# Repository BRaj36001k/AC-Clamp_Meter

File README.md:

**⚡ AC Clamp Meter**

A KiCad-based PCB design for a non-invasive AC measurement device using a Current Transformer (CT) sensor. Built as part of an EEE hardware project.
_____________________________________________________________
**📌 Overview**

This project implements an **AC Clamp Meter** circuit that measures alternating current without breaking the circuit. The design uses a split-core CT sensor, a signal conditioning front-end, and outputs a calibrated voltage proportional to the measured current.
---------------------------------------------------------------------------------------
|                Parameter              |                     Value                   |
|---------------------------------------|---------------------------------------------|
| Measurement Range                     |     0 – 110A AC (adjustable)                |
| CT Sensor                             |    SCT-013 / YHDC (30A or 100A variant)     |
| Output                                |          0–3.3V analog (ADC-ready)          |
| PCB Tool                              |                  KiCad 7.x                  |
---------------------------------------------------------------------------------------
______________________________________________________________
**🔌 How It Works**

CT Sensor (clamp)
      │
      ▼
3.5mm Jack Input
      │
      ▼
Signal Conditioning
(R1, R2, R3, R4 + D12 + C1)
      │
      ▼
Arduino Nano ADC Pin
      │
      ▼
Firmware Processing
      │
      ▼
I2C OLED Display
(GND / VCC / SDA / SCL)

__________________________________________________________________

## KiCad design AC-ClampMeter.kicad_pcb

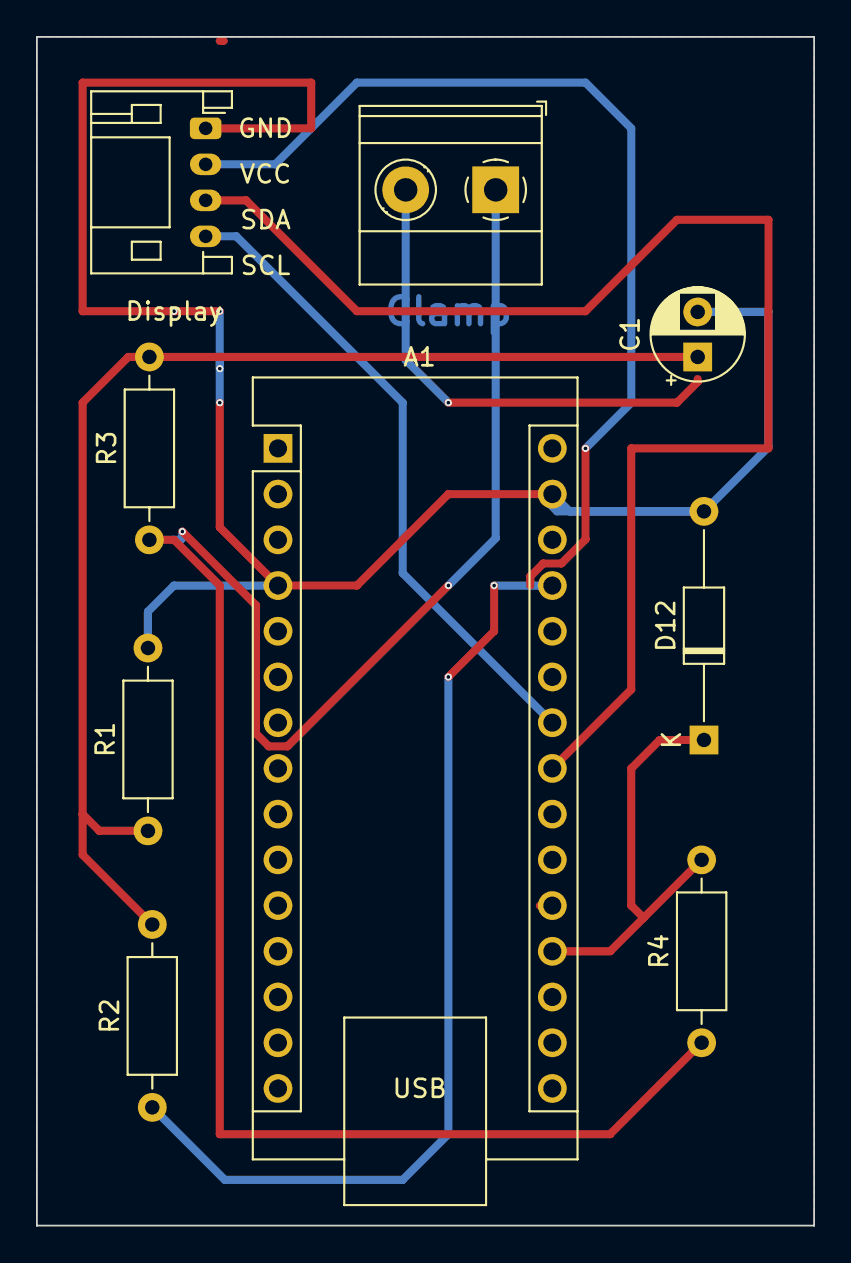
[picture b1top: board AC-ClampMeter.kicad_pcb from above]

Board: 2 copper layers, 43.2 x 66.0 mm, 8 parts (0 on the bottom side), 7 nets.

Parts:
A1: locked; Arduino_Nano
C1: 10uf 16V; CP_Radial_D5.0mm_P2.50mm
D12: 5V; D_DO-35_SOD27_P12.70mm_Horizontal
Display: 16x2 LCD with I2C; JST_PH_S4B-PH-K_1x04_P2.00mm_Horizontal
R1, R2: 10k; R_Axial_DIN0207_L6.3mm_D2.5mm_P10.16mm_Horizontal
R3: 68E; R_Axial_DIN0207_L6.3mm_D2.5mm_P10.16mm_Horizontal
R4: 1k; R_Axial_DIN0207_L6.3mm_D2.5mm_P10.16mm_Horizontal

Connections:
+5V: A1.27 (+5V), R2.1
A0: A1.19 (A0), D12.1 (K), R4.2
A4: A1.23 (A4), Display.3
A5: A1.24 (A5), Display.4
GND: A1.4 (GND), A1.29 (GND), C1.2, D12.2 (A), Display.1, R1.2
unnamed: C1.1, R1.1, R2.2, R3.2
unnamed: R3.1, R4.1
